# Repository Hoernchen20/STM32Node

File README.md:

# STM32Node

Simple prototyping board for LoRa with STM32F103 (BluePill) and RFM95

### Prerequisites

kicad 5

### Credits

https://github.com/myelin/myelin-kicad-libraries (STM32 module KiCad library)

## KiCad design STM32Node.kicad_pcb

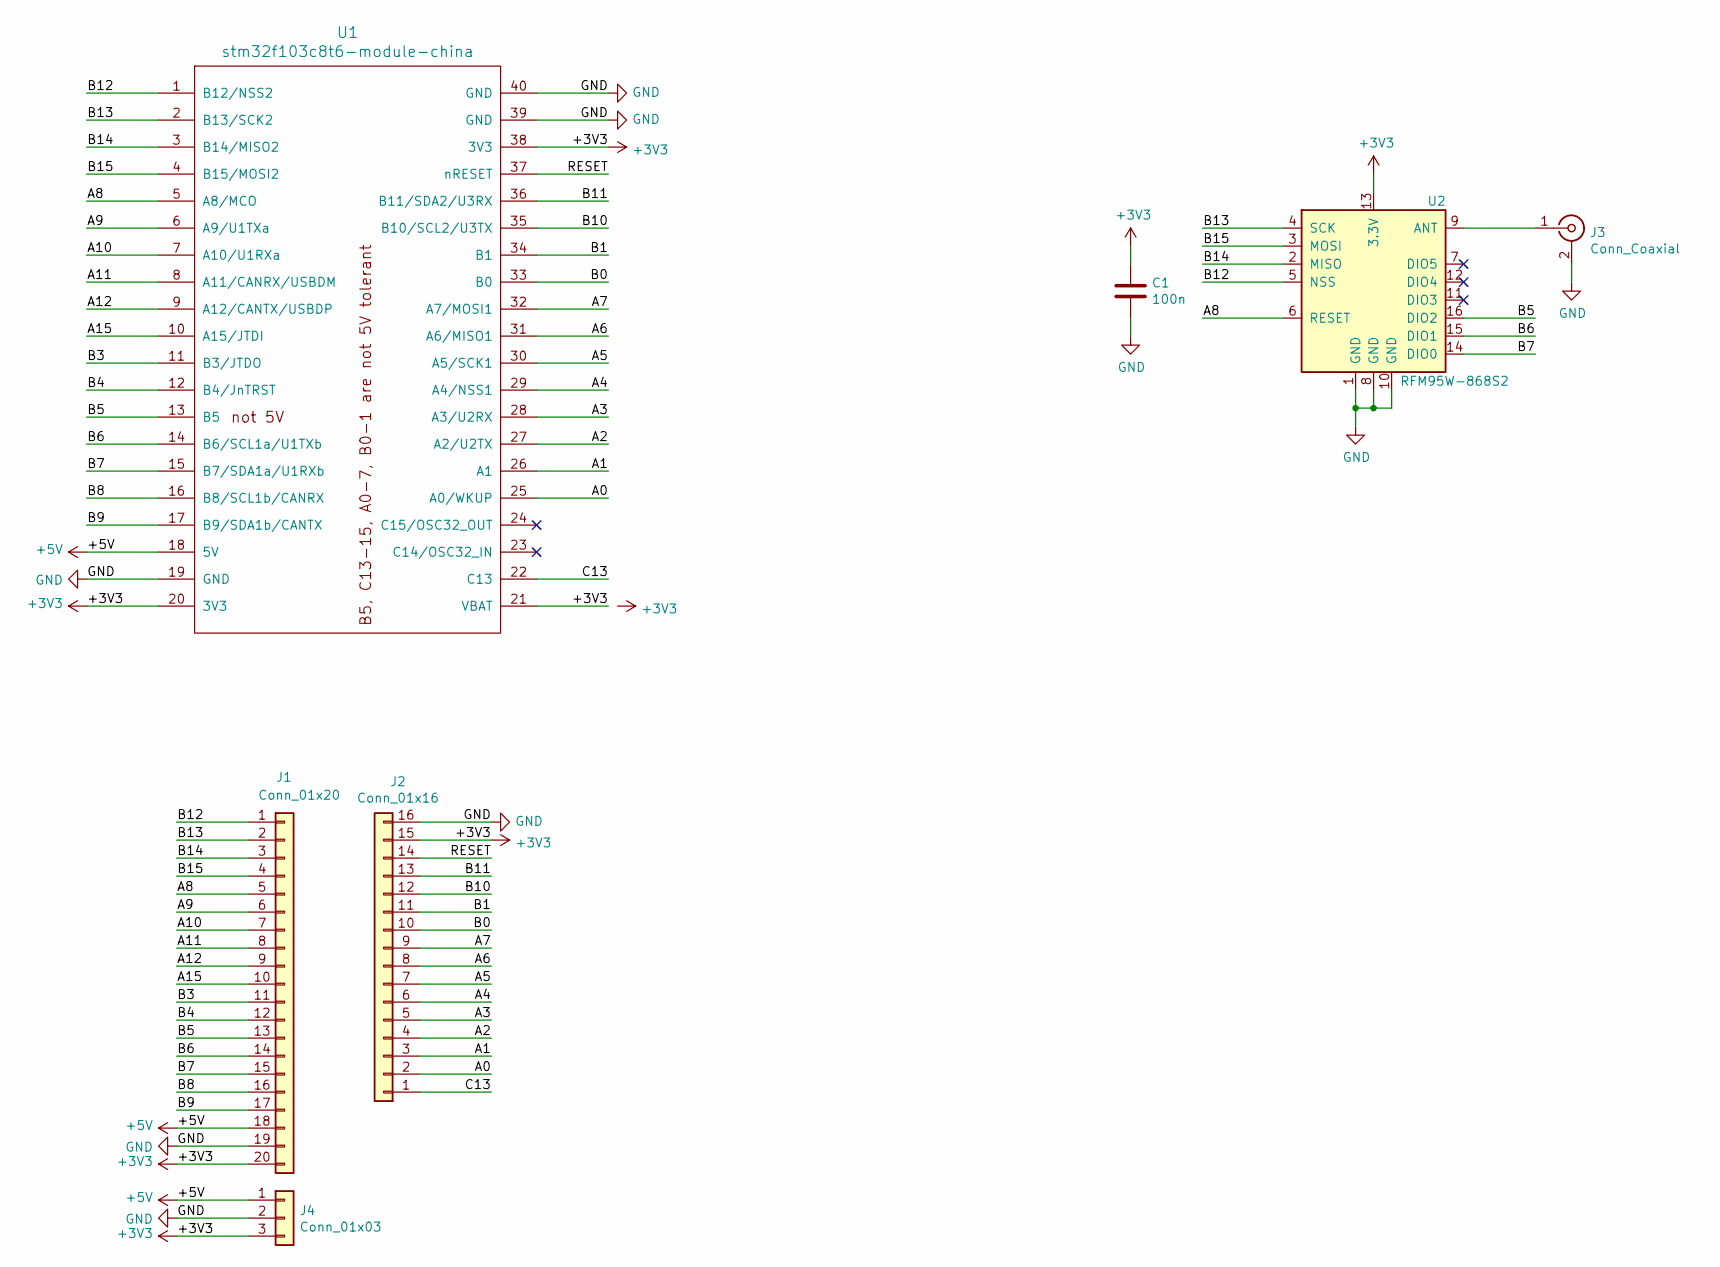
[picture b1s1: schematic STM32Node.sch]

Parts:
C1: 100n; C_0603_1608Metric
J1: Conn_01x20; PinSocket_1x20_P2.54mm_Vertical
J2: Conn_01x16; PinSocket_1x16_P2.54mm_Vertical
J3: Conn_Coaxial; U.FL_Molex_MCRF_73412-0110_Vertical
J4: Conn_01x03; PinSocket_1x03_P2.54mm_Vertical
U1: stm32f103c8t6-module-china
U2: RFM95W-868S2; HOPERF_RFM9XW_SMD

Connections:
+3V3: C1.1, J1.20, J2.15, J4.3, U1.20 (3V3), U1.21 (VBAT), U1.38 (3V3), U2.13 (3.3V)
+5V: J1.18, J4.1, U1.18 (5V)
/A0: J2.2, U1.25 (A0/WKUP)
/A1: J2.3, U1.26 (A1)
/A2: J2.4, U1.27 (A2/U2TX)
/A3: J2.5, U1.28 (A3/U2RX)
/A4: J2.6, U1.29 (A4/NSS1)
/A5: J2.7, U1.30 (A5/SCK1)
/A6: J2.8, U1.31 (A6/MISO1)
/A7: J2.9, U1.32 (A7/MOSI1)
/A8: J1.5, U1.5 (A8/MCO), U2.6 (RESET)
/A9: J1.6, U1.6 (A9/U1TXa)
/A10: J1.7, U1.7 (A10/U1RXa)
/A11: J1.8, U1.8 (A11/CANRX/USBDM)
/A12: J1.9, U1.9 (A12/CANTX/USBDP)
/A15: J1.10, U1.10 (A15/JTDI)
/B0: J2.10, U1.33 (B0)
/B1: J2.11, U1.34 (B1)
/B3: J1.11, U1.11 (B3/JTDO)
/B4: J1.12, U1.12 (B4/JnTRST)
/B5: J1.13, U1.13 (B5), U2.16 (DIO2)
/B6: J1.14, U1.14 (B6/SCL1a/U1TXb), U2.15 (DIO1)
/B7: J1.15, U1.15 (B7/SDA1a/U1RXb), U2.14 (DIO0)
/B8: J1.16, U1.16 (B8/SCL1b/CANRX)
/B9: J1.17, U1.17 (B9/SDA1b/CANTX)
/B10: J2.12, U1.35 (B10/SCL2/U3TX)
/B11: J2.13, U1.36 (B11/SDA2/U3RX)
/B12: J1.1, U1.1 (B12/NSS2), U2.5 (NSS)
/B13: J1.2, U1.2 (B13/SCK2), U2.4 (SCK)
/B14: J1.3, U1.3 (B14/MISO2), U2.2 (MISO)
/B15: J1.4, U1.4 (B15/MOSI2), U2.3 (MOSI)
/C13: J2.1, U1.22 (C13)
/RESET: J2.14, U1.37 (nRESET)
GND: C1.2, J1.19, J2.16, J3.2 (Ext), J4.2, U1.19 (GND), U1.39 (GND), U1.40 (GND), U2.1 (GND), U2.8 (GND), U2.10 (GND)
unnamed: J3.1 (In), U2.9 (ANT)

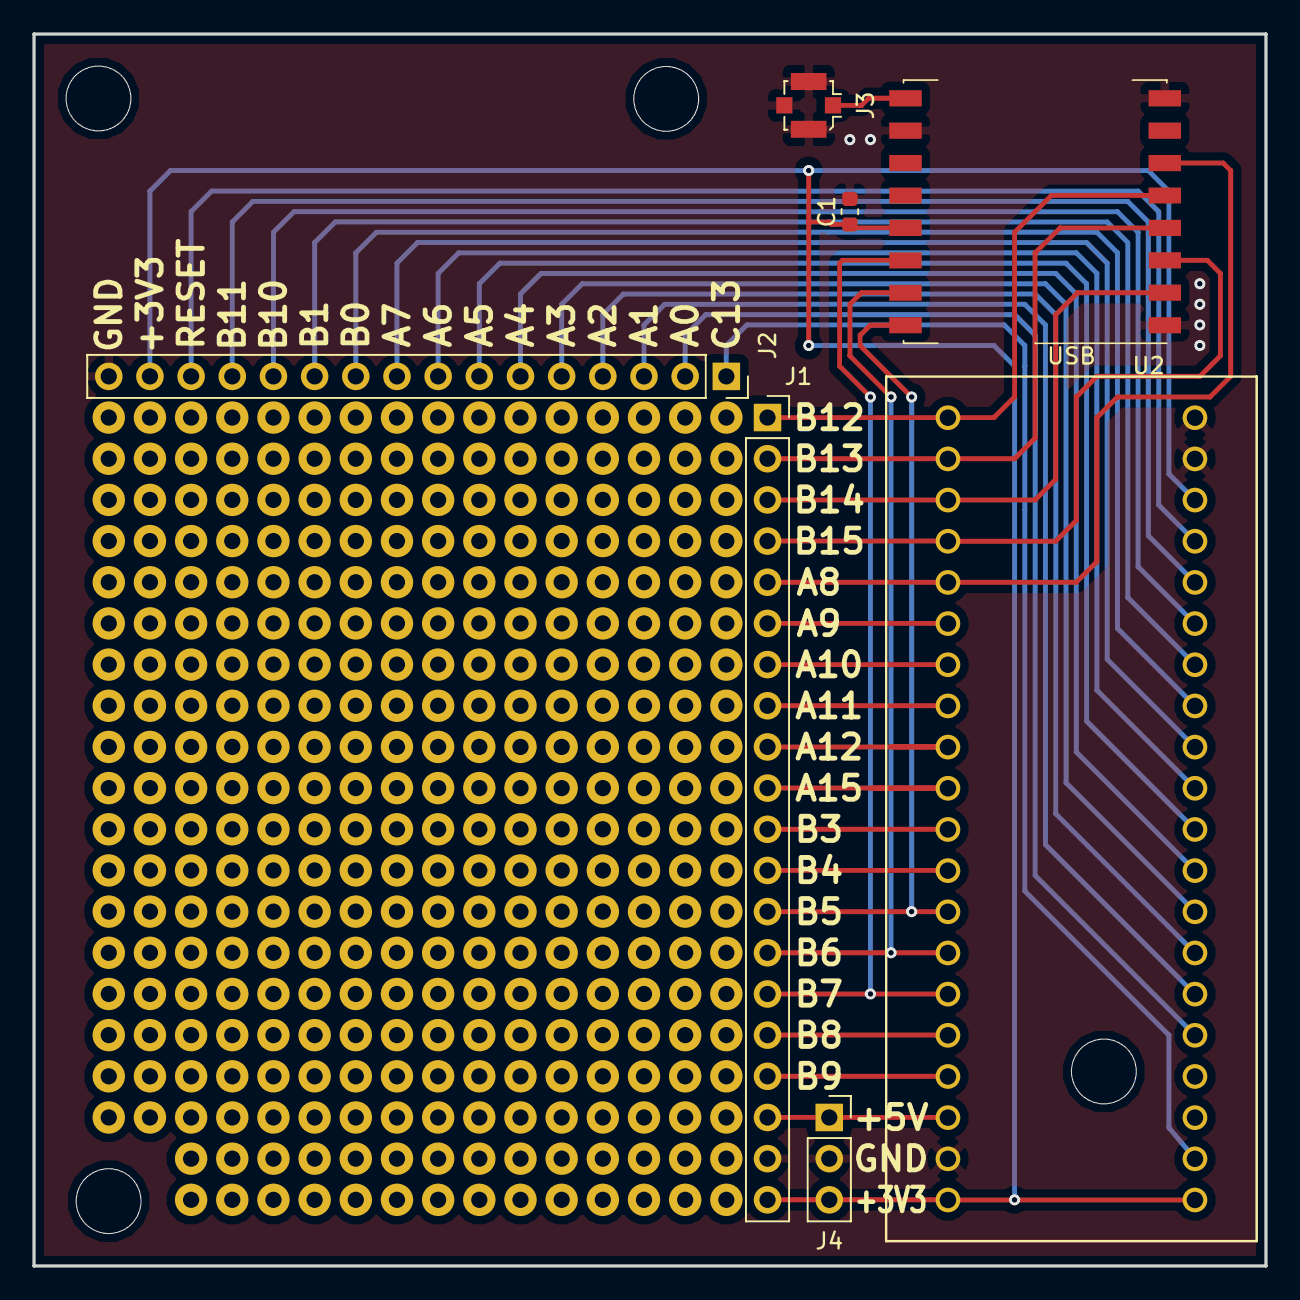
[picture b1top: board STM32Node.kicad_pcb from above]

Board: 2 copper layers, 76.0 x 76.0 mm, 7 parts (0 on the bottom side), 35 nets.

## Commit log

2018-12-09 Initialer Commit
2019-02-03 add 3D pictures
2019-02-03 add readme
2019-03-31 resize board, that it fits into case
